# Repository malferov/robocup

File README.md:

# RoboCup Junior

Netherlands team CoreX

# Components
- 25mm DC 12V GA-370 Low Speed Metal Gear Motor 400RPM 3.5 Watts 90 g
- TB6612FNG Dual Driver Controller Board MOSFET H Bridge 15V max VCC=2.7-5.5V Output 1.2A/3.2A
- 12.6V 3000mAh Lithium Ion Battery 157 g
- OT253-B47 Step-down buck converter 4.5-24V to 5V 3A
- HC-SR04 Ultrasonic Sensor
- TCRT5000 Reflective Infrared Optical Sensor
- TSSP4038, 38kHz IR Receiver, 950nm ±45°, 25m Range, 2.5-5.5V
- HC4067 16-channel Analog Multiplexer
- BMM150 Triple Axis Magnetometer Sensor
- MCU: ESP32-S3

# Metrics
### Consumption
- Main + CAM + Driver: 170 mA
### Performance
- Distance sensor: 33 ms
- Camera capture: 34 ms
- get_pos: 98 ms

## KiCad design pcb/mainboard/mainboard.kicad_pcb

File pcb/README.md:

# CNC

lift tool `G0 Z5`  
return to origin `G0 X0 Y0`

# PCB

default net class
- clearance 0.5 mm
- track width 1 mm
- via size 2 mm
- via hole 0.8

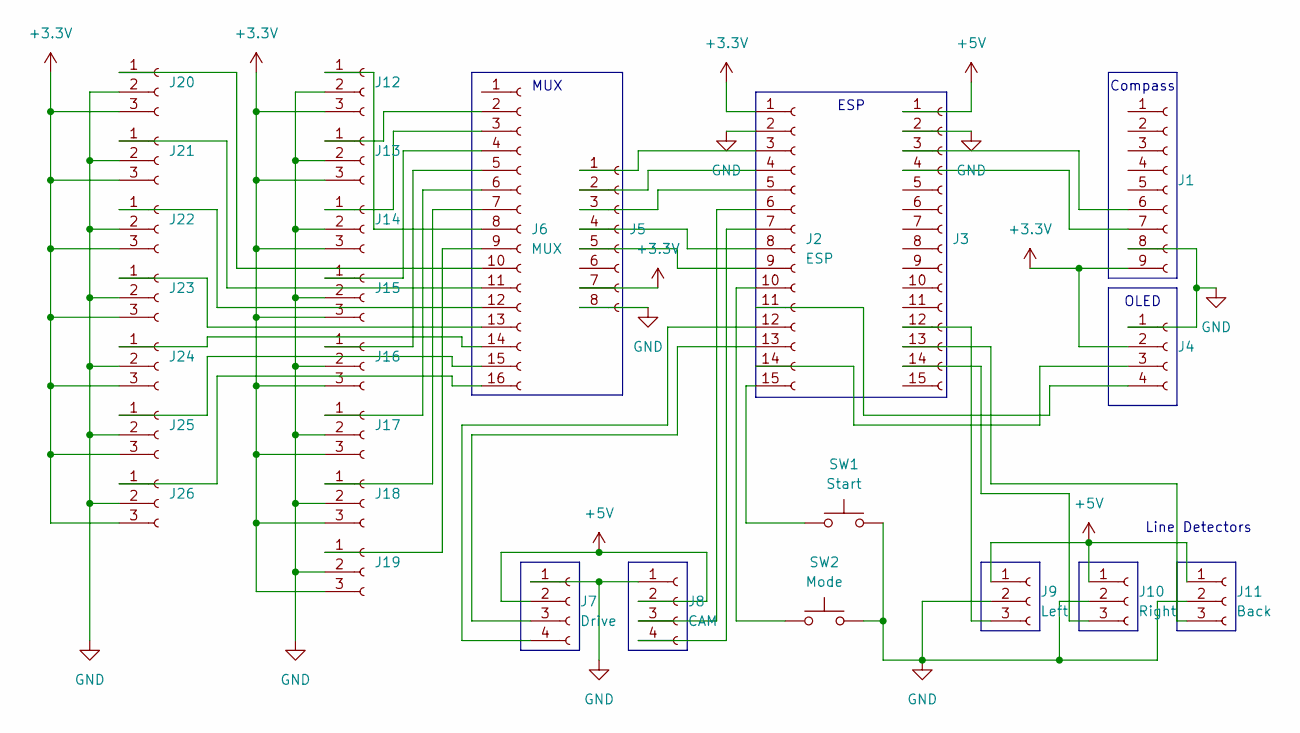
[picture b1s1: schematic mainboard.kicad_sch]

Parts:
J1: Compass; PinSocket_1x09_P2.54mm_Vertical
J2: ESP; PinSocket_1x15_P2.54mm_Vertical
J3: ESP_; PinSocket_1x15_P2.54mm_Vertical
J4: OLED; PinSocket_1x04_P2.54mm_Vertical
J5: MUX_; PinSocket_1x08_P2.54mm_Vertical
J6: MUX; PinSocket_1x16_P2.54mm_Vertical
J7: Drive; PinSocket_1x04_P2.54mm_Vertical
J8: CAM; PinSocket_1x04_P2.54mm_Vertical
J9: Left; PinSocket_1x03_P2.54mm_Vertical
J10: Right; PinSocket_1x03_P2.54mm_Vertical
J11: Back; PinSocket_1x03_P2.54mm_Vertical
J12, J13, J14, J15, J16, J17, J18, J19, J20, J21, J22, J23, J24, J25, J26: Conn_01x03_Socket; PinSocket_1x03_P2.54mm_Vertical
SW1: Start; D_5W_P5.08mm_Vertical_AnodeUp
SW2: Mode; D_5W_P5.08mm_Vertical_AnodeUp

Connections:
+3.3V: J1.9, J2.1, J4.2, J5.7, J12.3, J13.3, J14.3, J15.3, J16.3, J17.3, J18.3, J19.3, J20.3, J21.3, J22.3, J23.3, J24.3, J25.3, J26.3
+5V: J3.1, J7.2, J8.2, J9.1, J10.1, J11.1
GND: J1.8, J2.2, J3.2, J4.1, J5.8, J7.1, J8.1, J9.2, J10.2, J11.2, J12.2, J13.2, J14.2, J15.2, J16.2, J17.2, J18.2, J19.2, J20.2, J21.2, J22.2, J23.2, J24.2, J25.2, J26.2, SW1.2, SW2.2
unnamed: J1.6, J3.3
unnamed: J1.7, J3.4
unnamed: J2.3, J5.1
unnamed: J2.4, J5.2
unnamed: J2.5, J5.3
unnamed: J2.6, J8.3
unnamed: J2.7, J8.4
unnamed: J2.8, J5.4
unnamed: J2.9, J5.5
unnamed: J2.10, SW2.1
unnamed: J2.11, J4.4
unnamed: J2.12, J7.4
unnamed: J2.13, J7.3
unnamed: J2.14, J4.3
unnamed: J2.15, SW1.1
unnamed: J3.12, J9.3
unnamed: J3.14, J10.3
unnamed: J3.13, J11.3
unnamed: J6.8, J12.1
unnamed: J6.2, J13.1
unnamed: J6.3, J14.1
unnamed: J6.4, J15.1
unnamed: J6.5, J16.1
unnamed: J6.6, J17.1
unnamed: J6.7, J18.1
unnamed: J6.9, J19.1
unnamed: J6.10, J20.1
unnamed: J6.11, J21.1
unnamed: J6.12, J22.1
unnamed: J6.13, J23.1
unnamed: J6.14, J24.1
unnamed: J6.15, J25.1
unnamed: J6.16, J26.1

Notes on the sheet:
Line Detectors
OLED
Compass
ESP
MUX

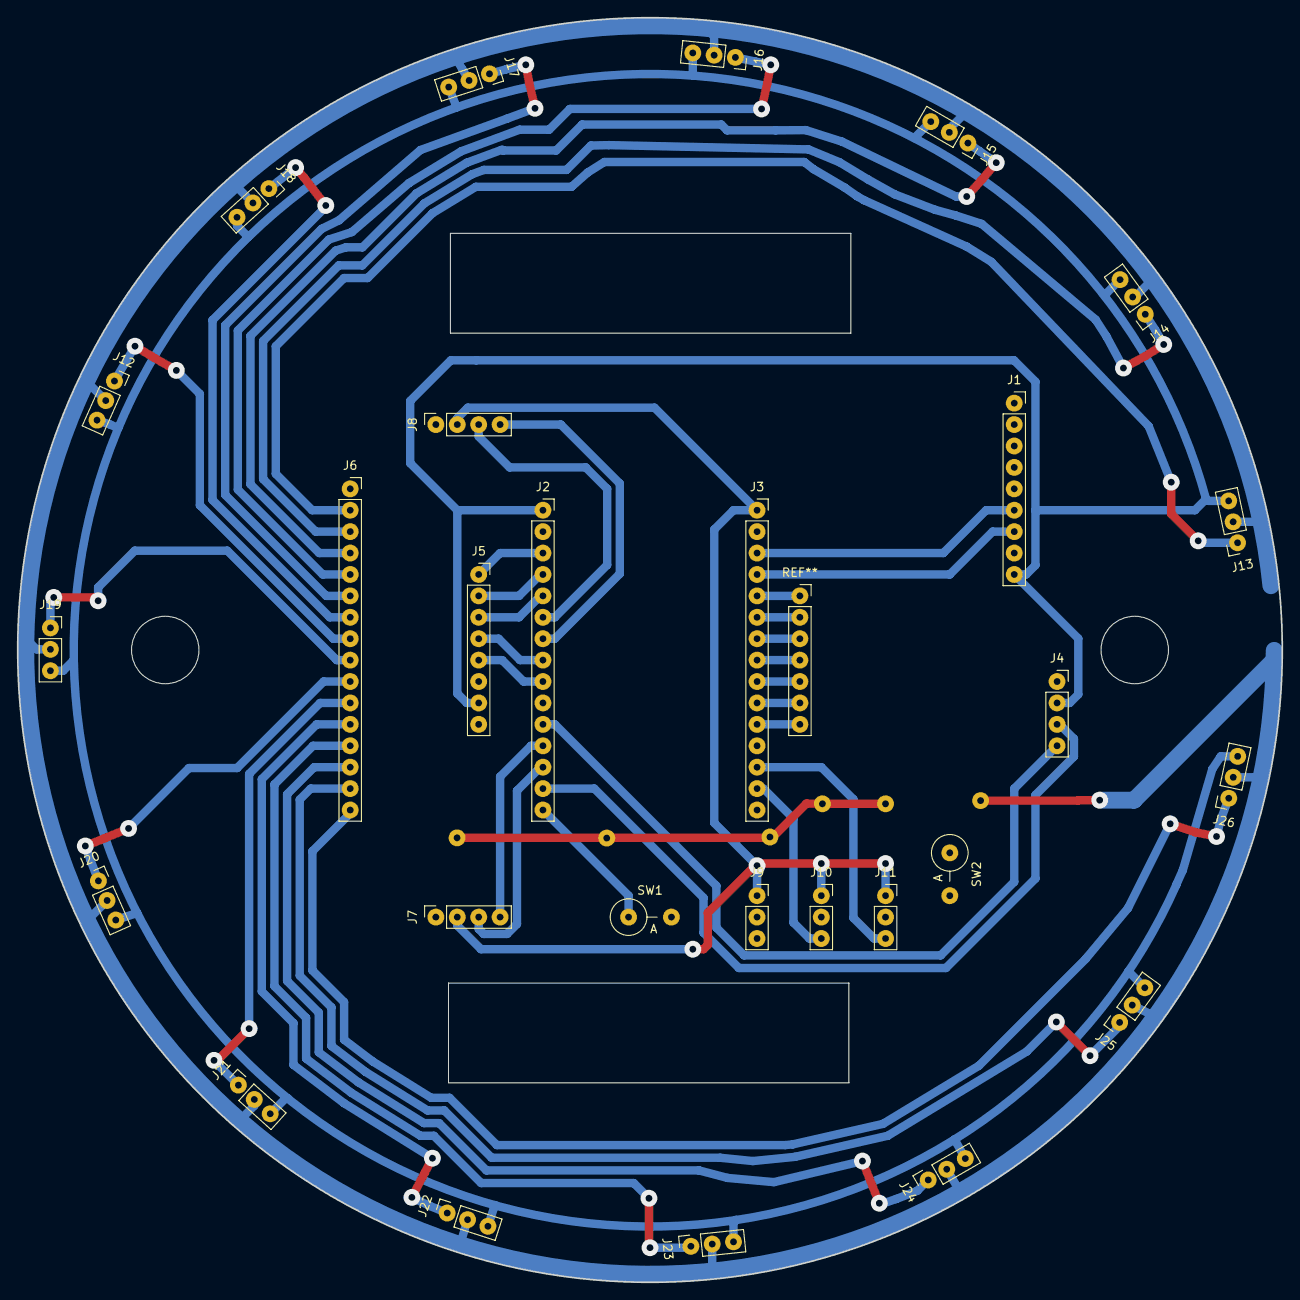
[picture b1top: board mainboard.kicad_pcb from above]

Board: 2 copper layers, 150.0 x 150.0 mm, 28 parts (0 on the bottom side), 36 nets.

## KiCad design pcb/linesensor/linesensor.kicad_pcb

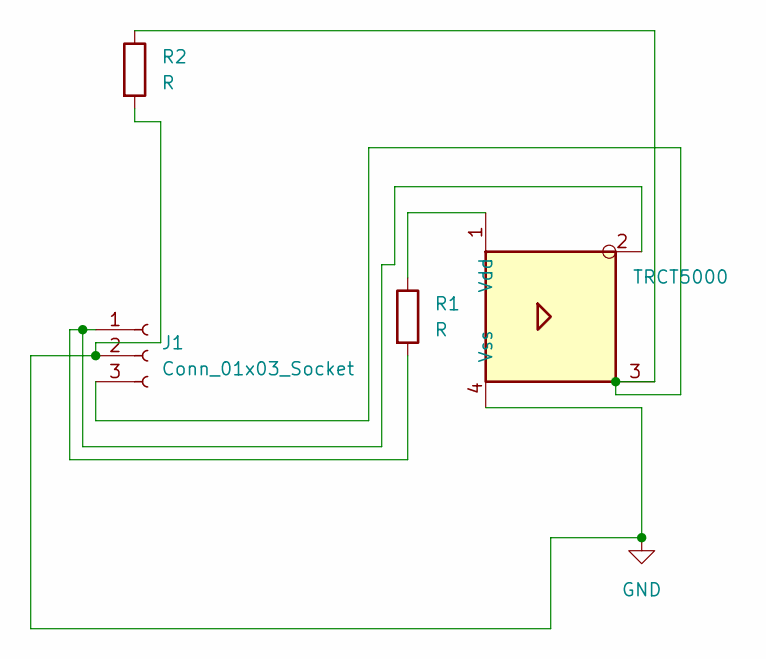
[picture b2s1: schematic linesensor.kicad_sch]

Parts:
J1: Conn_01x03_Socket; PinSocket_1x03_P2.54mm_Vertical
R1, R2: R; R_Axial_DIN0309_L9.0mm_D3.2mm_P12.70mm_Horizontal
U1: TRCT5000; CRT5000

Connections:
GND: J1.2, R2.2, U1.4 (Vss)
unnamed: J1.1, R1.2, U1.2
unnamed: J1.3, R2.1, U1.3
unnamed: R1.1, U1.1 (Vdd)

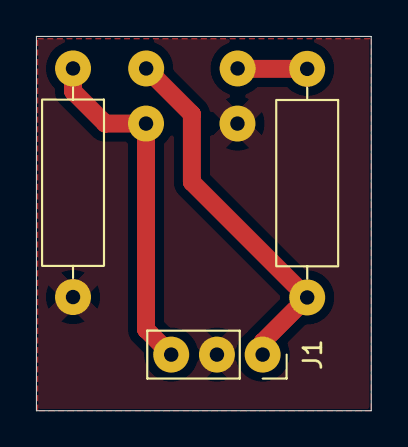
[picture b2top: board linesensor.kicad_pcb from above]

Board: 2 copper layers, 18.6 x 20.8 mm, 4 parts (0 on the bottom side), 4 nets.

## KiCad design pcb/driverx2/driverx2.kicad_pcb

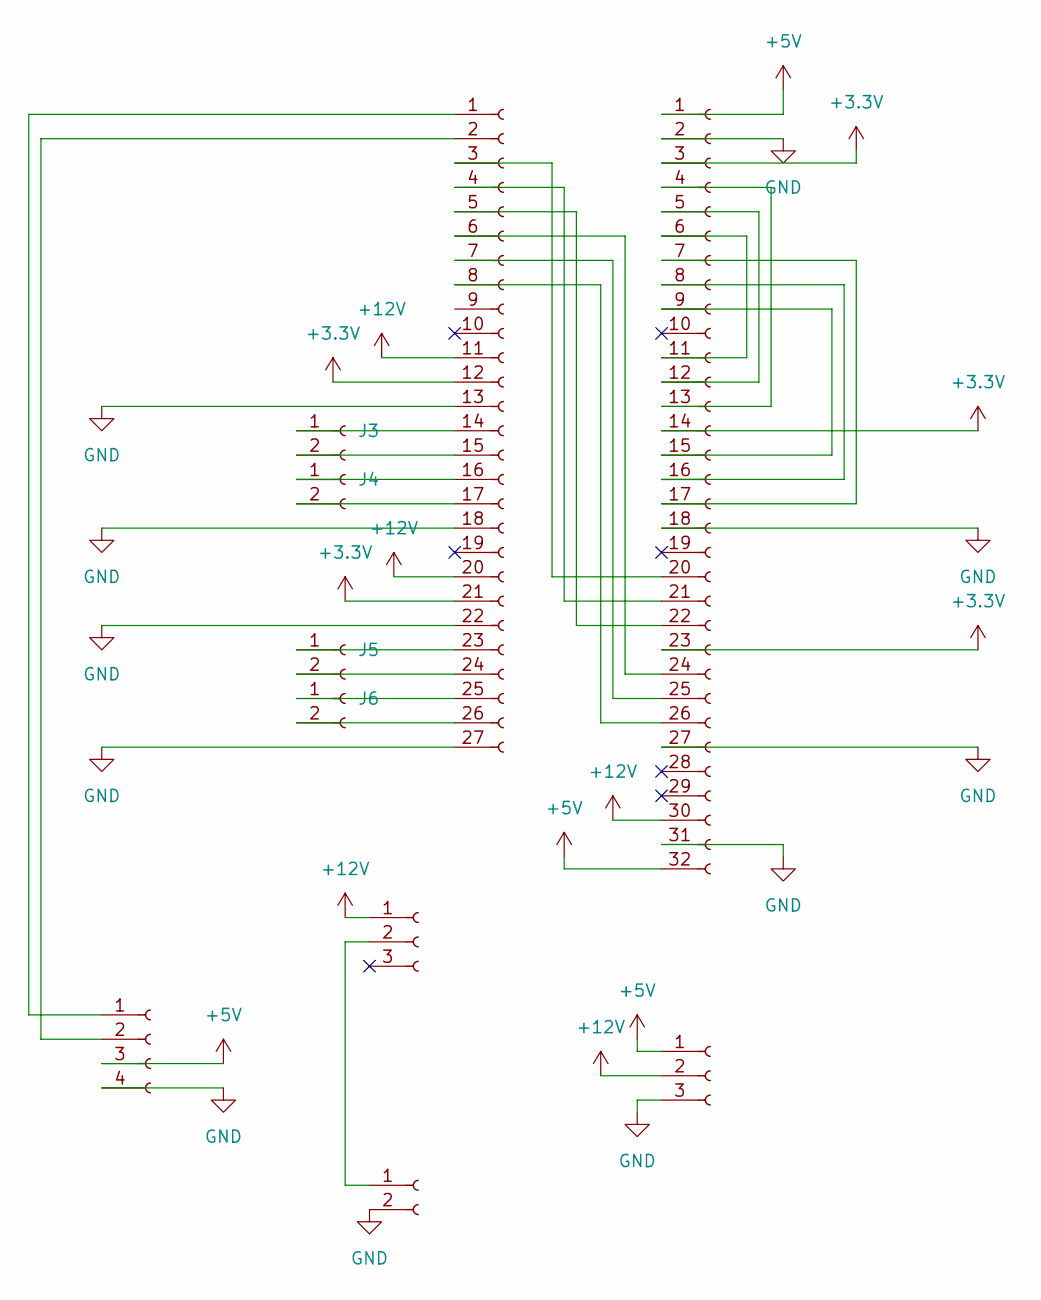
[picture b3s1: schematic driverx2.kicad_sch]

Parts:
J1: Conn_01x32_Socket; PinHeader_1x32_P2.54mm_Vertical
J2, J10: Conn_01x03_Socket; PinHeader_1x03_P2.54mm_Vertical
J3, J4, J5, J6, J9: Conn_01x02_Socket; PinHeader_1x02_P2.54mm_Vertical
J7: Conn_01x04_Socket; PinHeader_1x04_P2.54mm_Vertical
J8: Conn_01x27_Socket; PinHeader_1x27_P2.54mm_Vertical

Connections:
+3.3V: J1.3, J1.14, J1.23, J8.12, J8.21
+5V: J1.1, J1.32, J7.3, J10.1
+12V: J1.30, J2.1, J8.11, J8.20, J10.2
GND: J1.2, J1.18, J1.27, J1.31, J7.4, J8.13, J8.18, J8.22, J8.27, J9.2, J10.3
unnamed: J1.6, J1.11
unnamed: J1.5, J1.12
unnamed: J1.4, J1.13
unnamed: J1.9, J1.15
unnamed: J1.8, J1.16
unnamed: J1.7, J1.17
unnamed: J1.20, J8.3
unnamed: J1.21, J8.4
unnamed: J1.22, J8.5
unnamed: J1.24, J8.6
unnamed: J1.25, J8.7
unnamed: J1.26, J8.8
unnamed: J2.2, J9.1
unnamed: J3.1, J8.14
unnamed: J3.2, J8.15
unnamed: J4.1, J8.16
unnamed: J4.2, J8.17
unnamed: J5.1, J8.23
unnamed: J5.2, J8.24
unnamed: J6.1, J8.25
unnamed: J6.2, J8.26
unnamed: J7.1, J8.1
unnamed: J7.2, J8.2

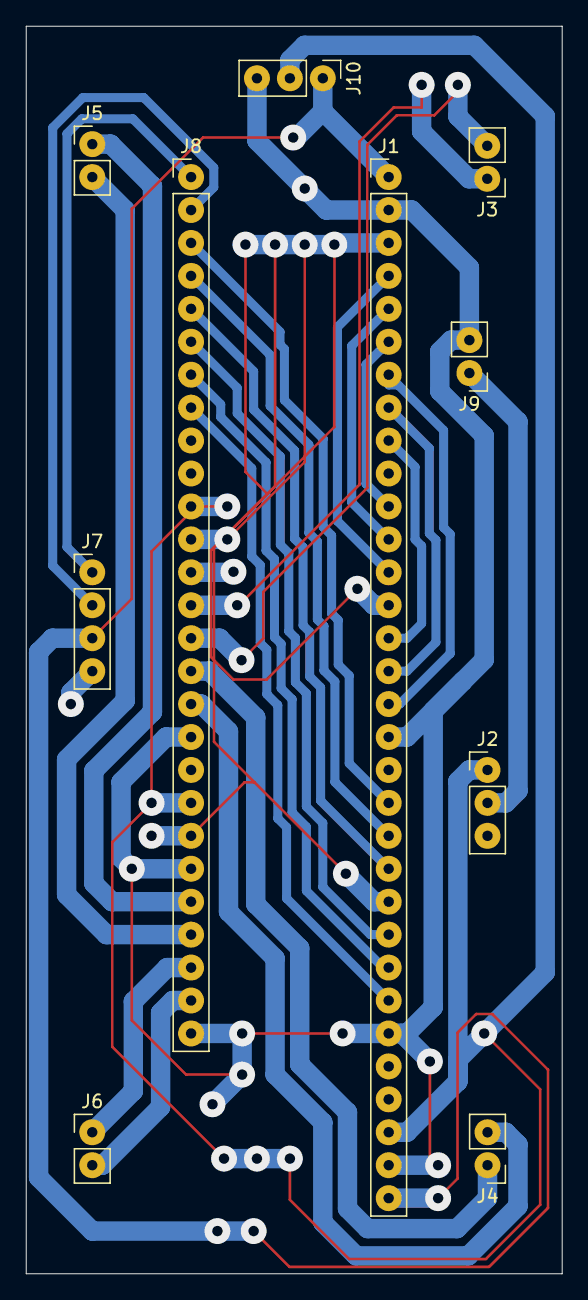
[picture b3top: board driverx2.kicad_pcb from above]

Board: 2 copper layers, 41.3 x 96.2 mm, 10 parts (0 on the bottom side), 27 nets.

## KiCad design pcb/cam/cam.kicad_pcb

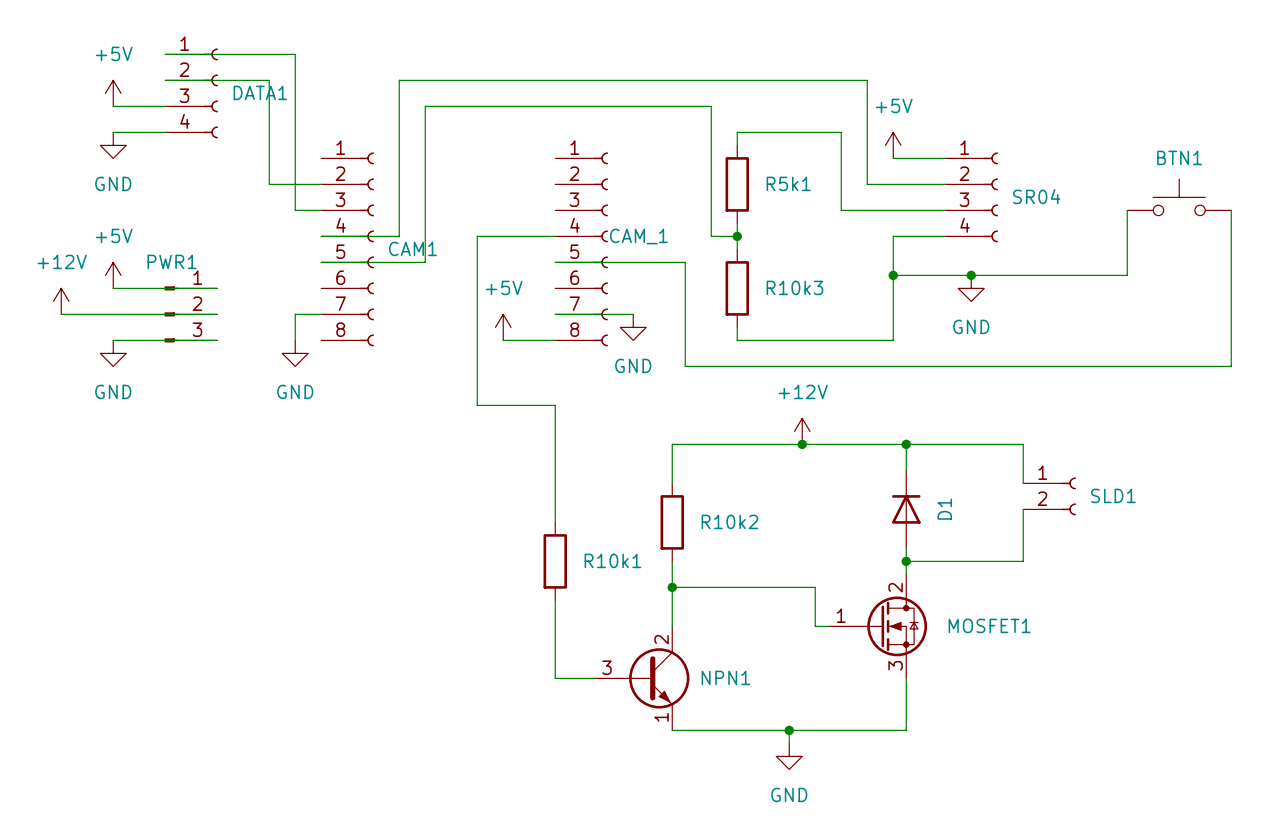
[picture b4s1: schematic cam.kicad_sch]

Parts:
BTN1: SW_Push; D_DO-41_SOD81_P5.08mm_Vertical_KathodeUp
CAM1: Conn_01x08_Socket; PinSocket_1x08_P2.54mm_Vertical
CAM_1: Conn_01x08_Socket; PinSocket_1x08_P2.54mm_Vertical
D1: 1N4001; D_DO-41_SOD81_P10.16mm_Horizontal
DATA1: Conn_01x04_Socket; PinSocket_1x04_P2.54mm_Vertical
MOSFET1: IRF840A; TO-220-3_Vertical
NPN1: 2SC1815; PinHeader_1x03_P2.54mm_Vertical
PWR1: Conn_01x03_Pin; PinHeader_1x03_P2.54mm_Vertical
R5k1, R10k1, R10k2, R10k3: R; R_Axial_DIN0207_L6.3mm_D2.5mm_P10.16mm_Horizontal
SLD1: Conn_01x02_Socket; PinHeader_1x02_P2.54mm_Vertical
SR04: Conn_01x04_Socket; PinSocket_1x04_P2.54mm_Vertical

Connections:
+5V: CAM_1.8, DATA1.3, PWR1.1, SR04.1
+12V: D1.1 (K), PWR1.2, R10k2.1, SLD1.1
GND: BTN1.1, CAM1.7, CAM_1.7, DATA1.4, MOSFET1.3 (S), NPN1.1 (E), PWR1.3, R10k3.2, SR04.4
unnamed: CAM1.2, DATA1.2
unnamed: CAM1.3, DATA1.1
unnamed: CAM1.4, SR04.2
unnamed: CAM1.5, R5k1.2, R10k3.1
unnamed: CAM_1.4, R10k1.1
unnamed: BTN1.2, CAM_1.5
unnamed: D1.2 (A), MOSFET1.2 (D), SLD1.2
unnamed: MOSFET1.1 (G), NPN1.2 (C), R10k2.2
unnamed: NPN1.3 (B), R10k1.2
unnamed: R5k1.1, SR04.3

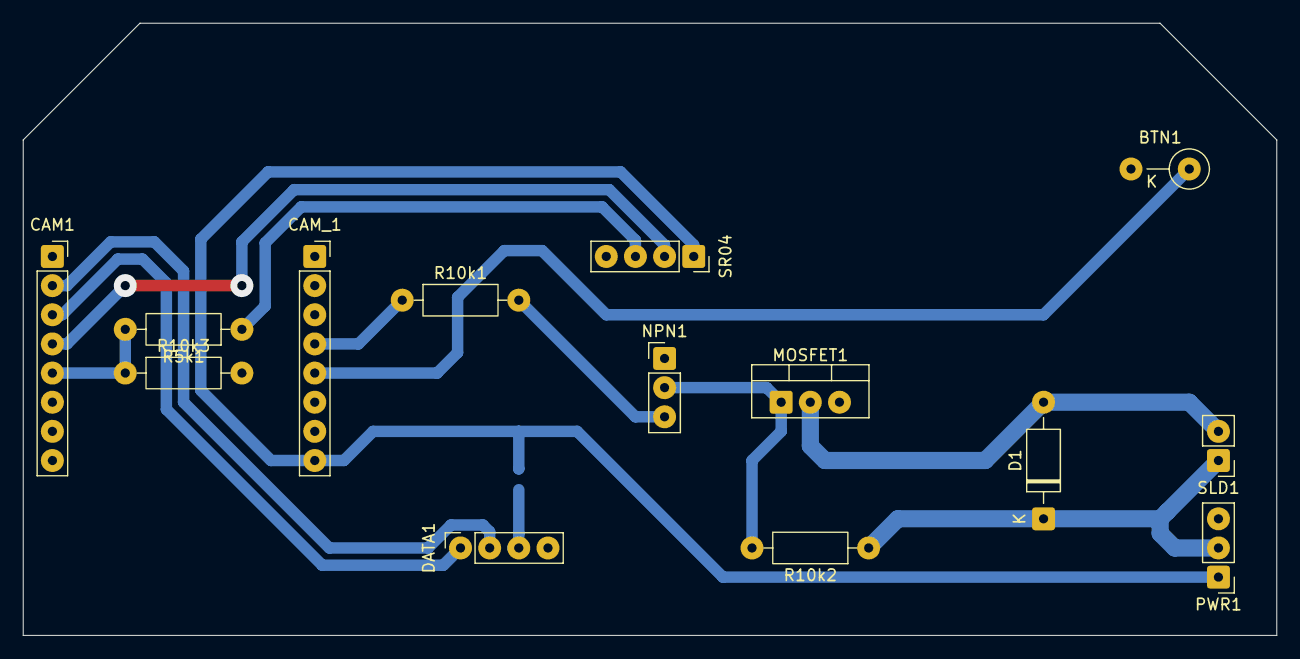
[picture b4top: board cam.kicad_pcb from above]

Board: 2 copper layers, 109.2 x 53.3 mm, 14 parts (0 on the bottom side), 13 nets.

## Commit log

2025-10-29 design draft
2025-11-23 pcb sensor
2025-11-26 wheel star image
2025-11-26 design docs
2025-11-26 small wheel pulley
2025-11-26 wheel cap
2025-11-27 Body details
2025-11-29 body init
2025-12-14 other teams posters
2025-12-14 chassis test
2025-12-14 docs components
2025-12-21 cam module
2025-12-26 move src
2025-12-26 update location
2025-12-27 cam capture
2025-12-29 debug version of camera code and base code
2025-12-29 fix cam
2025-12-29 fix direction
2025-12-30 width threshold
2026-01-12 Camera fix (#1)
2026-01-12 docs
2026-01-12 ball receiver
2026-01-18 multiple sensors
2026-01-20 driver pcb
2026-01-22 remove cache
2026-01-22 init
2026-01-23 fixup
2026-01-23 IR ball: read multiple sensors (#2)
2026-01-23 Mainboard PCB (#3)
2026-01-23 linesensor new
2026-01-25 body robo2 SVG
2026-01-29 IR ring
2026-01-29 IR ring (#4)
2026-01-30 S3 camera fixup (#5)
2026-02-03 CAM: distance sensor & kicker (#6)
2026-02-14 Integration IR ring (#7)
2026-02-17 clone motor driver
2026-02-18 motor test robo x2
2026-02-18 mainboardx2
2026-02-19 mill
2026-02-22 Clone robo x2 pcb (#8)
2026-02-22 ball search fix
2026-02-22 refine
2026-02-22 Integration solid move (#9)
2026-02-24 overshoot
2026-02-24 speed4
2026-02-25 logo
2026-02-25 Four wheels speed (#10)
2026-02-28 pins remapping
2026-02-28 mux_sig fix
2026-02-28 Bot2 adoptation (#11)
2026-03-01 Turning fix (#12)
2026-03-01 line endings
2026-03-01 modes
2026-03-03 average update
2026-03-03 Update components list in README.md
    Added additional components to the list in the README.
2026-03-03 fixed line sensor PCB
2026-03-03 Fix goal turning and mode select (#13)
2026-03-03 daylight
2026-03-03 Fix daylight (#14)
2026-03-04 calibration
2026-03-05 Mag compass (#15)
2026-03-06 linesensor
2026-03-07 hook
2026-03-07 Line sensor (#16)
2026-03-08 keeper comps
2026-03-08 motors target
2026-03-08 Motors target mode (#17)
2026-03-09 fixes
2026-03-09 kick
2026-03-09 Round ball (#18)
2026-04-16 BetterVersionStillBusyMenu
2026-04-16 Step 1, 2 ,3 done, no ToF, only CAL and TEST
2026-04-17 display distance fixup
2026-04-17 stable
2026-04-19 reroute mux_sig & mag
2026-04-19 lines logic
2026-04-19 Fix lines logic at TU Delft (#19)
2026-04-20 mainboard scheme update
